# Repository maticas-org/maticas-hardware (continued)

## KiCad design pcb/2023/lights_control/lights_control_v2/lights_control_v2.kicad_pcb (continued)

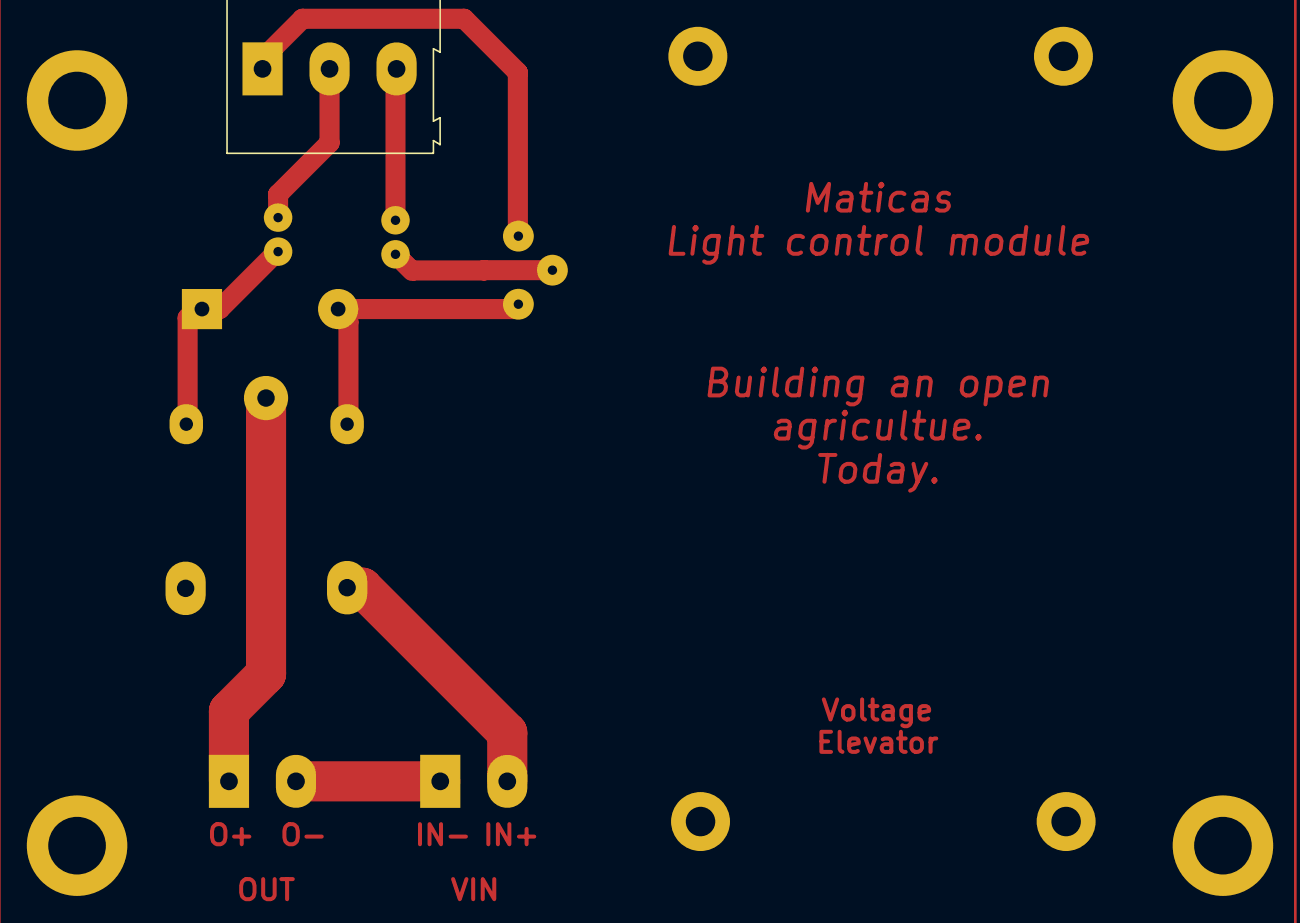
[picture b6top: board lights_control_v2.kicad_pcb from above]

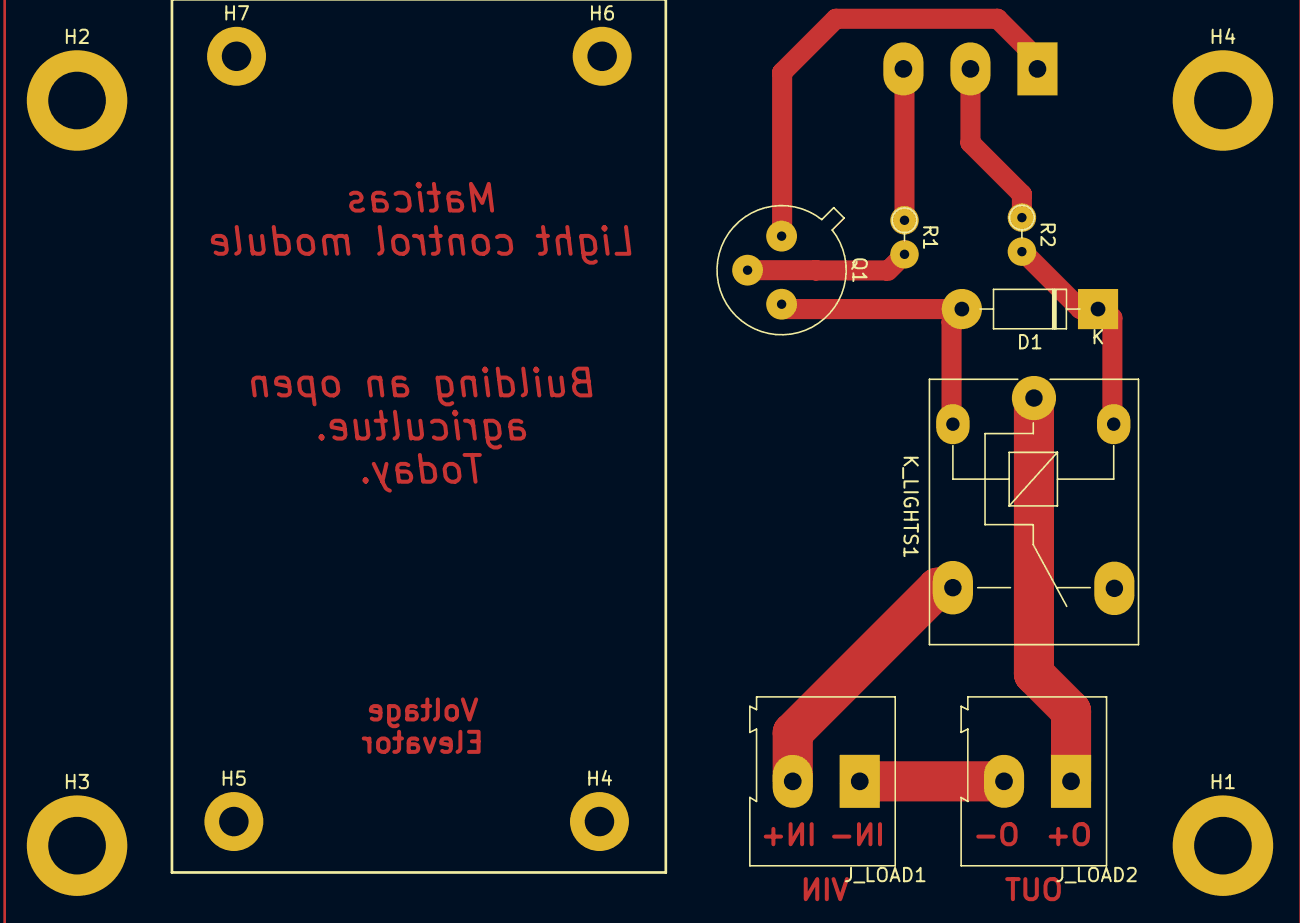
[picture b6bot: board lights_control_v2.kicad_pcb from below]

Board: 2 copper layers, 16 parts (15 on the bottom side), 9 nets.

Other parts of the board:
H4#2, H5, H6, H7: MountingHole; MountingHole_2.2mm_M2_Pad

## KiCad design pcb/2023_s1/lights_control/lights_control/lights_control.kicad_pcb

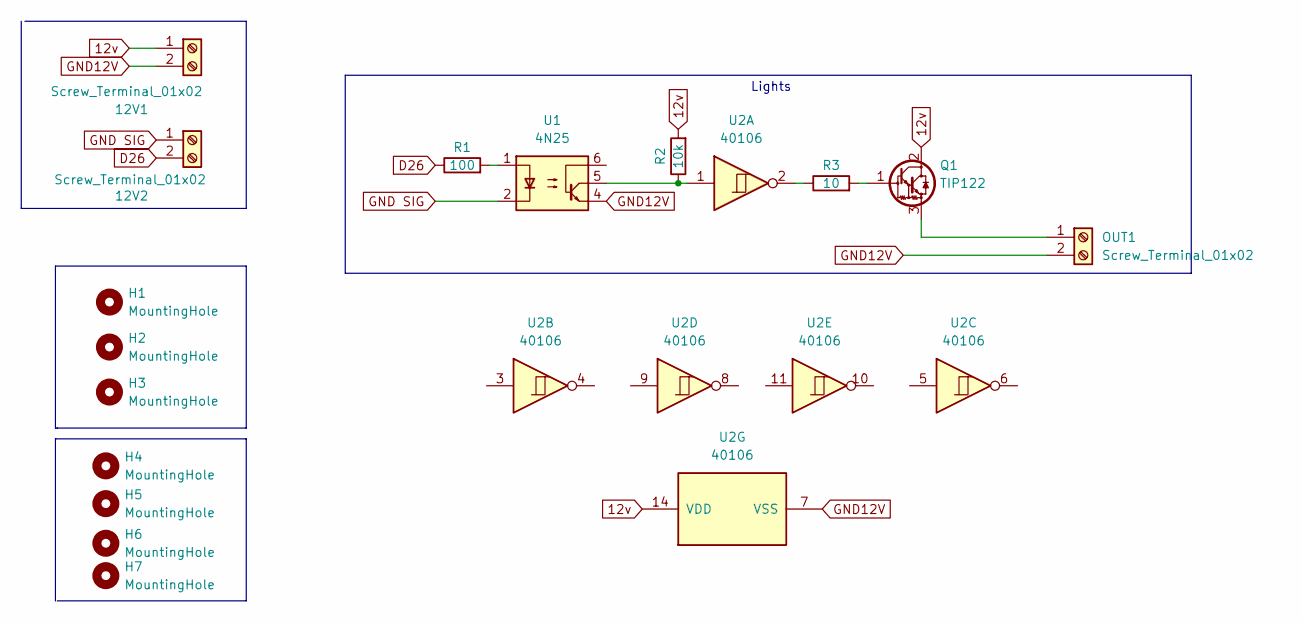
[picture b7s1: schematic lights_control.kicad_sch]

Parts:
12V1, 12V2: Screw_Terminal_01x02; Altech_AK300_1x02_P5.00mm_45-Degree
H1, H2, H3, H4, H5, H6, H7: MountingHole; MountingHole_2.2mm_M2_Pad
OUT1: Screw_Terminal_01x02; Altech_AK300_1x02_P5.00mm_45-Degree
Q1: TIP122; TO-220-3_Vertical
R1: 100; R_Axial_DIN0204_L3.6mm_D1.6mm_P2.54mm_Vertical
R2: 10k; R_Axial_DIN0204_L3.6mm_D1.6mm_P2.54mm_Vertical
R3: 10; R_Axial_DIN0204_L3.6mm_D1.6mm_P2.54mm_Vertical
U1: 4N25; DIP-6_W7.62mm
U2: 40106; DIP-14_W7.62mm

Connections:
12v: 12V1.1, Q1.2 (C), R2.2, U2.14 (VDD)
D26: 12V2.2, R1.1
GND12V: 12V1.2, OUT1.2, U1.4, U2.7 (VSS)
GND SIG: 12V2.1, U1.2
unnamed: OUT1.1, Q1.3 (E)
unnamed: Q1.1 (B), R3.2
unnamed: R1.2, U1.1
unnamed: R2.1, U1.5, U2.1
unnamed: R3.1, U2.2

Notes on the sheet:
Lights

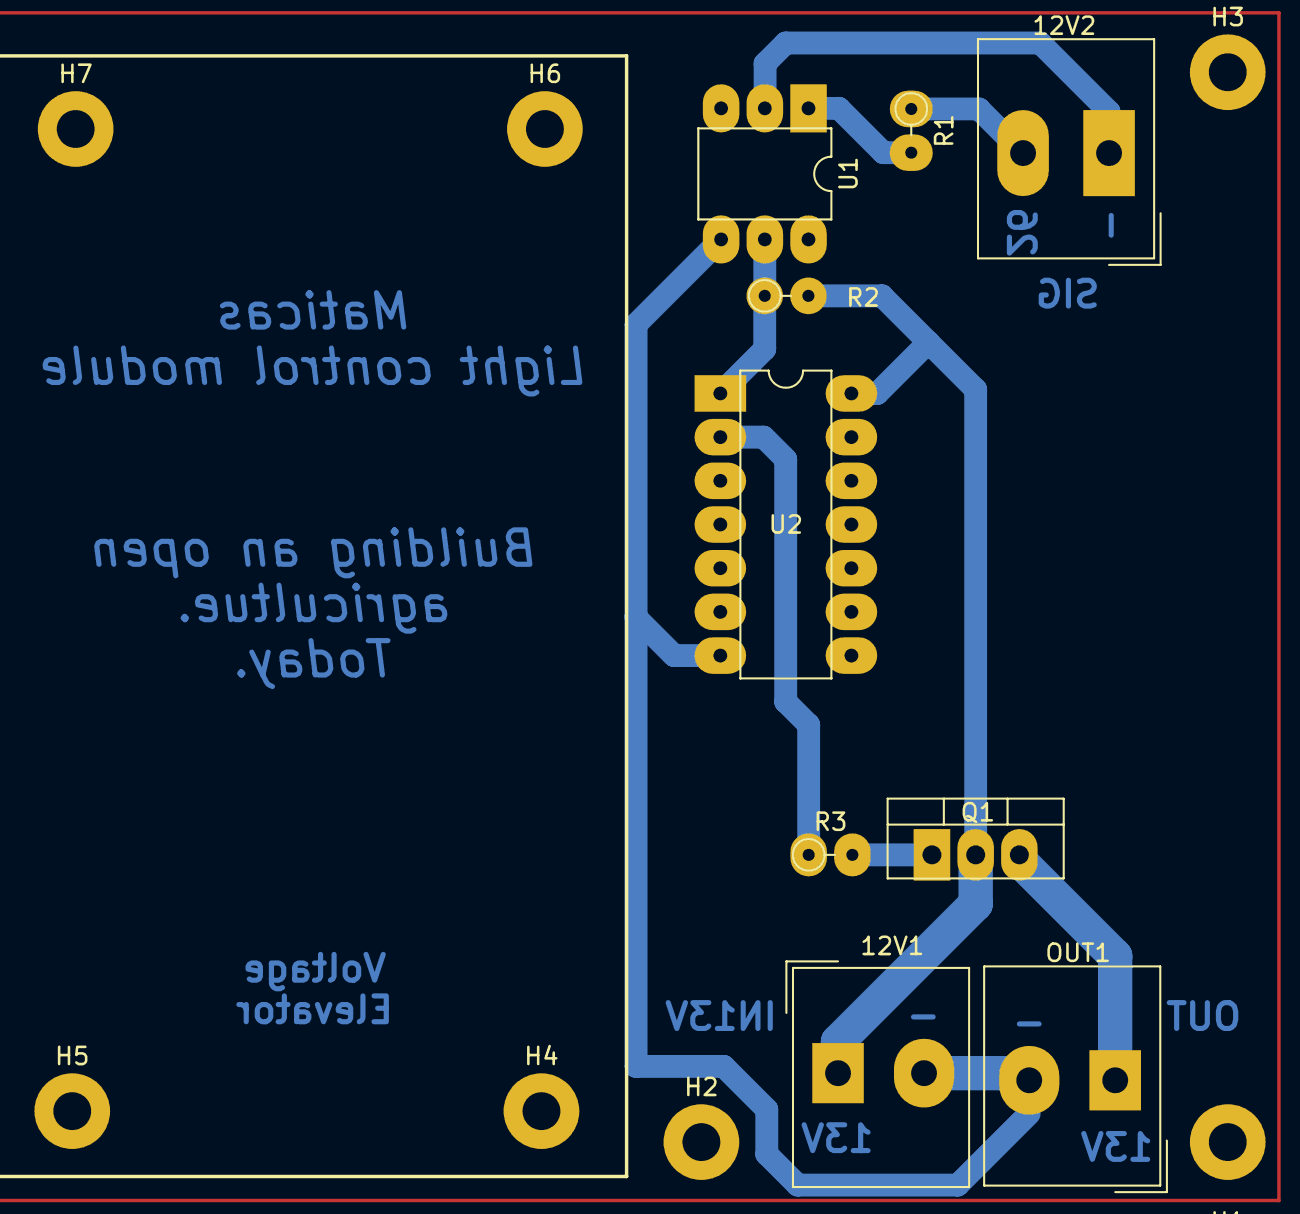
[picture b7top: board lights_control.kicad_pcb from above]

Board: 2 copper layers, 16 parts (0 on the bottom side), 9 nets.

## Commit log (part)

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2022-09-30 pcb design for esp32 board
2022-10-09 created solar battery pcb, revision of the design is needed
2022-10-09 create customary libraries to handle footprints and schematics which needs to be modified, given the production method we have now
2022-10-13 added micropython2 folder from initial maticas repo and it's hardware branch
2022-10-13 updated initialize_sensors and mqtt_and_module, now it works even if some sensor is unpluged
2022-10-13 changed the pub sub topics in config, and minor changes on BME280 script
2022-10-17 updated solar baterry charge pcb, by changing lm7805 for ams1117 voltage regulator, also repositioned the layout
2022-10-19 added deepsleep and time measurement (time on it takes to send all the data)
2022-10-20 added diode to esp32 board and updated solar board to fixed 5.0v ams1117
2022-10-20 added 2 pairs of male pins to measure solar panel voltage and battery voltage
2022-11-12 added new sensors, battery voltage, and panel voltage
2022-11-12 added new sensor, dht11
2022-11-12 added new pins to connect more 3.3v sensors and 5.0v sensors, also added 2 pull up resistors for sda and scl pins
2022-11-12 updated tp4056 holes position
2022-11-15 changed the pull up from 5v to 3.3v
2022-11-15 changed the pad size and shape of the pull up resistors
2022-12-03 new pcb for controling power devices from esp32
2022-12-03 update, testing pcb components layout and extended control and power pcb
2022-12-05 backup, updating footprints of extended circuit
2023-02-20 update, started new pcb
2023-02-28 water tank update, adn separation into control and power module
2023-02-28 updated pad sizes
2023-03-03 update, added 3d shapes for the pieces, and added capacitor
2023-03-06 added, added fabrication outputs
2023-03-08 corrected power control pcb, and repositioned most of the elements
2023-03-11 update, added mounting holes
2023-03-14 update, finished connecting the power pcb module, and added the fan control to both pcbs
2023-03-14 fix, fixed positioning of esp32, it was mirrored
2023-03-16 fix, separated the light control into another pcb, due to the different voltage it handles and confort for the use
2023-03-16 addition, added 3 mounting holes to the pcb, need to add voltage reduction and a better transistor to turn on and off the led lights
2023-03-17 update, renamed the folders
2023-03-22 fix, added a 4th mounting hole and rerouted the pcb in order to make feasible to solder given our poor infrastructure for PCB production
2023-03-22 fix, added a 4th mounting hole
2023-03-22 fix, changed small naming
2023-04-02 update, reselection of output pins and ds18b20 pin, rerouting and resizing of pads
2023-04-10 update, new export files and added voltage elevator space for lights control pcb
2023-04-22 update, made some pads bigger for better soldering
2023-04-25 update, changed some terminals to screw terminals for easyer connection
2023-04-29 update, routed lights pcb
2023-04-29 update, reestructured code folders to start a new approach based on previous ones
2023-04-30 update, renamed folders, and built simple control routine
2023-04-30 update, test folder
2023-05-01 update, based on experience and practice connecting AC devices proposed a change to the pcb, to make it easier to connect, and more intuitive
2023-05-01 fix, bug fixes after testing with live connection
2023-05-01 update, proposed changes on power PCB
2023-05-03 update, fixed lights pcb, only lacks rerouting
2023-05-06 fix, the trigger schmith was not powered in the PCB
2023-05-09 fix, reconnected to internet periodically and build a better internet connection function
2023-05-10 new, started new and easier approach to turn ON and OFF the lights
2023-05-11 fix, forgot to use 2N2222 as current amplifier of the input signal
2023-05-11 update, changed the periodic wifi reconnection to a periodic reboot instead, which does have the same effect but also pretends to compensate for periodic failures in wifi connection and controlling t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
2023-05-12 update, changed pcbs to use mechanic relays instead of the trigger schmith circuit, because of reliability and simpleness of the design
2023-05-12 changed timing of rebooting and turns off all the actuators before rebooting
2023-05-15 update, changed addition time overload to return a time object, changed scheduler time delta to count for the total minutes elapsed, changed the fan operation times
2023-05-15 update, added functios which convert time to total minutes, seconds or hours of the day
2023-06-01 built ambient measurement module
2023-06-01 update, fixed some bugs
2023-06-01 update, added an important resistor
2023-06-06 update, changed the time the esp32 waits to connect to the internet
2023-06-06 update, repositioned through holes
2023-06-10 update, removed periodic reboot because it was causing unexpected behaviour, particularly the esp32 won't come back to live after rebooting, only after a manual reboot it'd start to work again
2023-06-10 update, changed the dht22 pin from 2 to 25, added a ceramic capacitor, and rerouted some elements
2023-06-10 update, repositioned sensors and rf module so we can use shorter tracks and looks better
2023-06-12 add, added a micropython web server which allows to change hydroponic system settings
2023-06-12 create, created the integration1 module, which is the combination into one PCB of the signal_esp32 and power_control PCB
2023-06-12 update, created a class sensor module and renamed the Module class to actuatorModule, in order to be able to take measurements with the scheduler
2023-06-13 update, debugged code, ds18b20 readings and ec readings are working along with the scheduler, remaining to test with live actuators
2023-06-15 update, routed the integration PCB, only production and testing is remaining
2023-06-16 update, now the requests are being sent to the esp32 as a post, and it has to process the input data yet
2023-06-19 update, changed the way the time requests are done, now the request is only made at boot and after some defined time has passed like 12h for example, meanwhile the local millis are used to determine 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
2023-06-20 rename, reestructured the 2023 PCBs development folders, the idea is to separate the modules into the ones that use an rf antena and the ones which only use the esp32 with wifi
2023-06-20 update, rerouted paths and added text to the pcb
2023-06-22 renamed, reestructured code into folders and changed path of imports inside py files, in order to have a better organized code structure
2023-06-22 addition, added robust2 and simple2 modules for stablishing mqtt connection, the mqtt connection is not working yet
2023-06-23 update, there was a bug when an actuator had no exec object associated to the pin, not it's fixed
2023-07-10 update, minor bug fixies
2023-08-04 add, added second revision integration pcb update
2023-08-08 add, added new type of pcb
2023-08-10 add, new experimental model to take to the market
2023-08-11 new updates
2023-08-12 small refactor, due to memory constraints we decided to separate the development code from the deploy code, the development code is the friendly code, which is well documented, and the rawcode is the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
2023-08-13 add, finished building html server which allows changing configuration of the individual actuator
2023-08-13 add, added capabilities of storing measurements for display, for the user
2023-08-16 tested new small feature
2023-08-20 update, refactored for cleaner code
2023-08-20 update, fixed bugs
2023-08-21 update, removed unsustainable dependencies, the QRCode consumed alot of memory and made the module overlow multiple times, so now the raw ip is displayed, and instead of QRCode now we can display mat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
2023-08-22 add, small class diagram to document a bit, the general idea of the code in there
2023-08-23 update, bug fixed, now web server also implements a timeout on the connection recieve, and gives a response for when too many requests are being made
2023-08-24 add, added custom solid state relay to the PCB by using optocouplers and triacs, also added the MOC3041 footprint to the esp32 library to keep it within our common resources
2023-08-24 update, fixed an error in the PCB and now any AC appliance which get's connected can work
2023-09-01 update, fixed bug on the PCB, a wrong connection between the BT136 and the actuators wasn't making it work
2023-09-01 update, fixed bug on the PCB, a pull up resistor is required for the DHT11 to work well, so now it's added
2023-09-02 update, fixed small bug around time aritmethics, a modulo operator was needed to deal with += and -= operations between time objects in the hour field, this was causing bugs
2023-12-07 Update
    expanded code, now testing and tuning remains to be done
2023-12-11 Rename
2023-12-11 Update
    Further tested the connection module, added ping capabilities and tested it, also separated classes into different specific files, so that only one class is defined inside each file, added the api cl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
    TODO: test the read and write mechanisms of the data_management_microservice and the data_storage_module, it's also necessary to test the API module with a dummy API.
2023-12-14 Update event.py
    added common exception for unhandled status response, further tested the interconnection between clases, connection event manager, sensors micro service and data management micro service are fully de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
    1. Time event manager (adding RTC code and example).
    2. Sensor adapters (DHT11 and VEML 7700 live tests).
    3. Database read and write of a file on an SD card instead of a file in the ESP32 memory.
    4. API client test of data emission to a dummy API.
2024-01-30 Add
    ante un cambio de situaciones no es raro cambiar de parecer, vamos a probar con arduino debido a inestabilidad del código python
2024-02-03 keep on iterating
2024-02-04 working as intended for now
2024-02-09 Update
    further works now DataManagementService remains to be fully developed, and finally the API client
2024-02-11 Update
    now writes to sdcard, sometimes...
2024-02-19 Add library
2024-02-19 Update main.ino
    Now datamanagement service only stores data if connection event manager is not able to send it
2024-02-19 Update
    Adds api client to connection event manager, so that it can send the data from sensor microservice also
2024-02-22 Unnecesary
2024-02-22 Update
    Version working nearly as intended, only remains to add the logic for sending all the files in the SD card, may be in the future it would be important to add to the event class a flag which specifies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
2024-02-26 Update
    now uses "file" as global variable and changed the format of data in the DHTadapter, so that resembles the data that Django can consume
2024-02-26 Update
    bug fixes so that the data gets stored and turned into string in the right way.
2024-02-26 Update main.ino
    Now sends the stored data through the API
2024-02-26 Update Event.cpp
    small but important bugfix
2024-02-26 Update SDCard.cpp
    bugfix
2024-02-26 Update ApiClient.h
    set a smaller timeout
2024-02-26 Add
    added logging and credentials to log the sensor to the API
2024-03-05 Update
    code changes for debugging and trying to get rid of possible cause problems
2024-03-06 Continued testing
    now async use of notify for the connection event manager causes some trouble
2024-03-06 Bugs
2024-03-07 Add
    Created 3rd code, seems way less buggy
2024-03-08 Update, further testing
    seems to work well
2024-03-12 Update
    updates to write to the endpoint
2024-03-13 Update ApiClient.h
    Now if gets 'HTTP_ERROR_INVALID_RESPONSE' status asumes that data was sent succesfully but esp32 was not able to understand the response, and maps this to an OK_STATUS
2024-03-13 Update Event.cpp
    Renaming of field in order to make it usable by the django api
2024-03-13 Update SDCard.cpp
    File existence check before deletion to avoid bugs
2024-03-13 Update SensorAdapters.h
    "timestamp" field renaming to make it usable for the django API
